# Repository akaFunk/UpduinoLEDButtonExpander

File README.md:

# Simple LED and button expander for the Upduino v2.0
This is a very simple expander for the Upduino v2.0 FPGA development/evaluation board. It contains four buttons and LEDs which is enought for a hello world course in FPGA development. All components are absolute standard and should be found at every electronics distributor.

## Images

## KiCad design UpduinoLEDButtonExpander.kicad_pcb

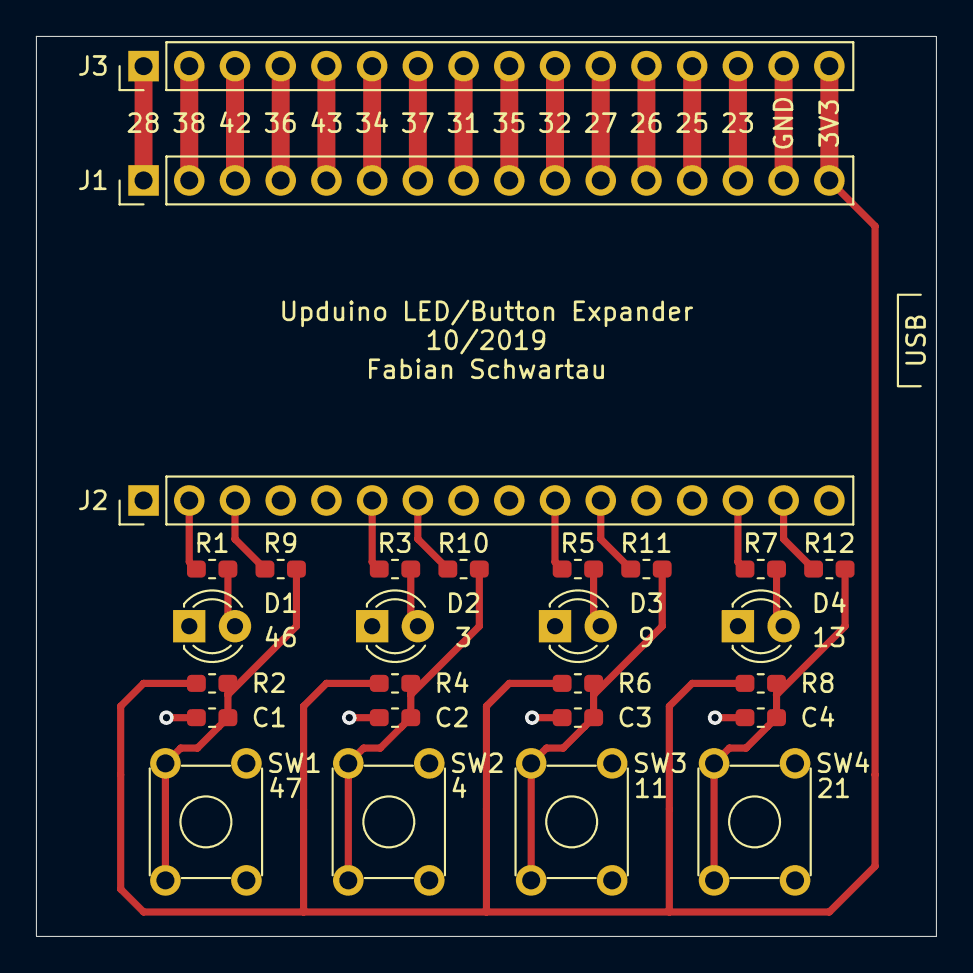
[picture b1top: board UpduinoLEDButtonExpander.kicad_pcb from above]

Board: 2 copper layers, 50.0 x 50.0 mm, 27 parts (0 on the bottom side), 32 nets.

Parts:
C1, C2, C3, C4: 100n; C_0603_1608Metric_Pad1.05x0.95mm_HandSolder
D1, D2, D3, D4: LED; LED_D3.0mm_Clear
J1, J2, J3: Upduino2; PinHeader_1x16_P2.54mm_Vertical
R1, R3, R5, R7, R9, R10, R11, R12: 220; R_0603_1608Metric_Pad1.05x0.95mm_HandSolder
R2, R4, R6, R8: 10k; R_0603_1608Metric_Pad1.05x0.95mm_HandSolder
SW1, SW2, SW3, SW4: SW_Push_Dual; SW_TH_Tactile_Omron_B3F-10xx

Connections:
+3V3: J1.16, J3.16, R2.2, R4.2, R6.2, R8.2
/3: J2.6, R3.1
/4: J2.7, R10.1
/9: J2.10, R5.1
/11: J2.11, R11.1
/13: J2.14, R7.1
/21: J2.15, R12.1
/23: J1.14, J3.14
/25: J1.13, J3.13
/26: J1.12, J3.12
/27: J1.11, J3.11
/28: J1.1, J3.1
/31: J1.8, J3.8
/32: J1.10, J3.10
/34: J1.6, J3.6
/35: J1.9, J3.9
/36: J1.4, J3.4
/37: J1.7, J3.7
/38: J1.2, J3.2
/42: J1.3, J3.3
/43: J1.5, J3.5
/46: J2.2, R1.1
/47: J2.3, R9.1
GND: C1.2, C2.2, C3.2, C4.2, D1.1, D2.1, D3.1, D4.1, J1.15, J3.15, SW1.1, SW1.2, SW2.1, SW2.2, SW3.1, SW3.2, SW4.1, SW4.2
unnamed: C1.1, R2.1, R9.2, SW1.3, SW1.4
unnamed: C2.1, R4.1, R10.2, SW2.3, SW2.4
unnamed: C3.1, R6.1, R11.2, SW3.3, SW3.4
unnamed: C4.1, R8.1, R12.2, SW4.3, SW4.4
unnamed: D1.2, R1.2
unnamed: D2.2, R3.2
unnamed: D3.2, R5.2
unnamed: D4.2, R7.2

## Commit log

2019-09-28 Added additional protection resistor for the buttons
2019-09-28 Added Edge-Cuts gerber file
2019-09-28 Updated pdf files
2019-09-28 Updated 3D image
2019-09-29 Added Solder Mask Gerber files
2019-10-13 Corrected button symbol, added more labels
2019-10-14 Added license
